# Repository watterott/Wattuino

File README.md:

# Wattuino
Arduino compatible Boards and Modules.

* [Wattuino Board Support Package](https://learn.watterott.com/arduino/watterott-boards) for Arduino IDE.
* [Documentation on learn.watterott.com](https://learn.watterott.com)
* Open-Source and released under the [Creative Commons Attribution Share-Alike License](https://creativecommons.org/licenses/by-sa/4.0/).

## Wattuino RC

* Microchip **SAMW25** Module (SAMD21 ARM Cortex-M0+ and WINC1500 WiFi/WLAN SoC)
* USB CDC+MSC Bootloader (Arduino compatible)
* 5V tolerant IOs
* Dual Full-Bridge Motor Drivers (Allegro Micro A3909)
* MicroUSB connector for programming/communication
* PCB Size: 70mm x 50mm

## Wattuino Uno

* Microchip AVR **ATmega328P** @ 16 MHz (external resonator)
* OptiBoot Bootloader with auto baud rate detection (Arduino compatible)
* FTDI FT231X USB-UART-Bridge
* USB-B or MicroUSB connector for programming/communication
* PCB Size: 68.58mm x 53.34mm

## Wattuino Pro Mini

* Microchip AVR **ATmega328P** @ 16 MHz or 8 MHz (external resonator)
* OptiBoot Bootloader with auto baud rate detection (Arduino compatible)
* All pins of the AVR are available (also ADC6, ADC7)
* FTDI connector for programming/communication
* PCB Size: 33.02mm x 17.78mm

## Wattuino Pro Mini PB

* Microchip AVR **ATmega328PB** @ 16 MHz or 8 MHz (external resonator)
* OptiBoot Bootloader with auto baud rate detection (Arduino compatible)
* All pins of the AVR are available (also PE0/SDA1, PE1/SCL1, PE2/ADC6, PE3/ADC7)
* FTDI connector for programming/communication
* PCB Size: 33.02mm x 17.78mm

## Wattuino Nanite 841

* Microchip AVR **ATtiny841** @ 8 MHz (internal clock) with USART, SPI, I2C Slave, ADC, EEPROM
* Micronucleus USB Bootloader (Arduino compatible)
* Designed by [cpldcpu](https://github.com/cpldcpu)
* 14-Pin DIP and pin-compatible with 14-Pin SOIC ATtiny841
* MicroUSB connector for programming/communication
* PCB Size: 24.13mm x 10.16mm

## Wattuino Nanite 85

* Microchip AVR **ATtiny85** @ 16.5 MHz (internal clock) with USI, ADC, EEPROM
* Micronucleus USB Bootloader (Arduino compatible)
* Based on the original [Nanite 85](https://github.com/cpldcpu/Nanite) design by [cpldcpu](https://github.com/cpldcpu)
* Pin-compatible with 8-Pin DIP ATtiny85
* MicroUSB connector for programming/communication
* PCB Size: 17.46mm x 10.16mm

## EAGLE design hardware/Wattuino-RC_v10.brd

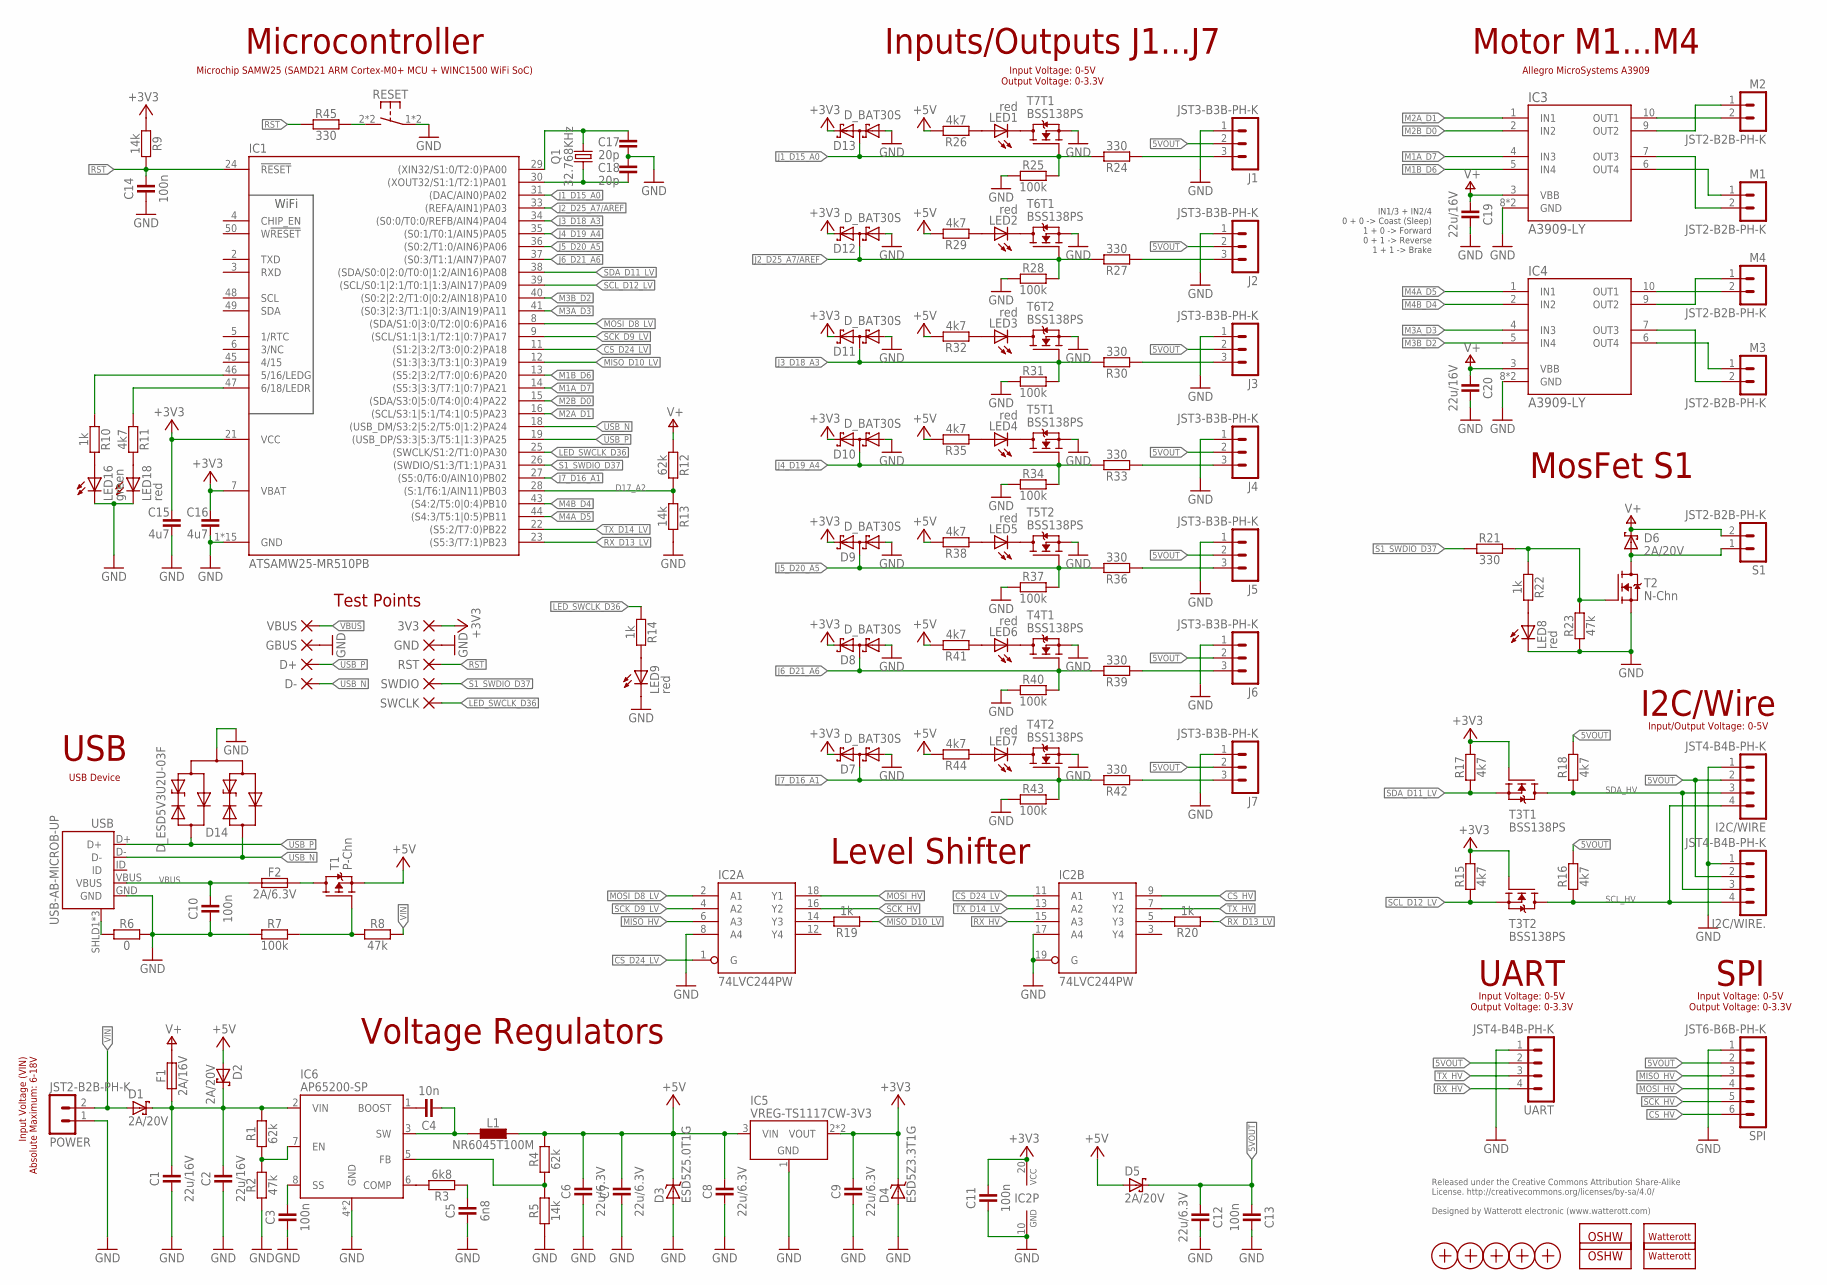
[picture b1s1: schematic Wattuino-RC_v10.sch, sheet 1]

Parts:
3V3: PAD-1.0_NC
C1, C2, C19, C20: 22u/16V; C0805
C3, C10, C11, C13, C14: 100n; C0402
C4: 10n; C0402
C5: 6n8; C0402
C6, C7, C8, C9, C12: 22u/6.3V; C0805
C15, C16: 4u7; C0603
C17, C18: 20p; C0402
D1, D2, D5, D6: 2A/20V; SMA_DO214AC
D3: ESD5Z5.0T1G; SOD523
D4: ESD5Z3.3T1G; SOD523
D7, D8, D9, D10, D11, D12, D13: D_BAT30S; SOT323
D14: D_ESD5V3U2U-03F; SOT723
D+: PAD-1.0_NC
D-: PAD-1.0_NC
F1: 2A/16V; C1812
F2: 2A/6.3V; C1206
GBUS: PAD-1.0_NC
GND: PAD-1.0_NC
I2C/WIRE, I2C/WIRE.: JST4-B4B-PH-K; JST_B4B-PH-K
IC1: ATSAMW25-MR510PB; ATSAMW25-MRX10
IC2: 74LVC244PW; TSSOP20
IC3, IC4: A3909-LY; MSOP10-PAD
IC5: VREG-TS1117CW-3V3; SOT223
IC6: AP65200-SP; SO08-PAD
J1, J2, J3, J4, J5, J6, J7: JST3-B3B-PH-K; JST_B3B-PH-K
L1: NR6045T100M; L_NR60XX
LED1, LED2, LED3, LED4, LED5, LED6, LED7, LED8, LED9, LED18: red; C0603
LED16: green; C0603
LOGO1: OSHW_LOGOX0100; OSHW_6X100
LOGO2: OSHW_LOGOX0150; OSHW_6X150
LOGO3: LOGO-S_PLACE_S; SPARK_TPLACE_S
LOGO4: LOGO-PLACE; LOGO_TPLACE
M1, M2, M3, M4: JST2-B2B-PH-K; JST_B2B-PH-K
POWER: JST2-B2B-PH-K; JST_B2B-PH-K
Q1: 32.768KHz; CRYSTAL_ZM315
R1, R4, R12: 62k; C0402
R2, R8, R23: 47k; C0402
R3: 6k8; C0402
R5, R9, R13: 14k; C0402
R6: 0; C0402
R7, R25, R28, R31, R34, R37, R40, R43: 100k; C0402
R10, R14, R19, R20, R22: 1k; C0402
R11, R15, R16, R17, R18, R26, R29, R32, R35, R38, R41, R44: 4k7; C0402
R21, R24, R27, R30, R33, R36, R39, R42, R45: 330; C0402
RESET: SW-TACTILE-TL3305C; TL3305; MPN TL3305C
RST: PAD-1.0_NC
S1: JST2-B2B-PH-K; JST_B2B-PH-K
SPI: JST6-B6B-PH-K; JST_B6B-PH-K
SWCLK: PAD-1.0_NC
SWDIO: PAD-1.0_NC
T1: P-Chn; SOT23
T2: N-Chn; SOT23
T3, T4, T5, T6, T7: BSS138PS; SOT363
UART: JST4-B4B-PH-K; JST_B4B-PH-K
USB: USB-AB-MICROB-UP; USB-MICROB-1051330011
VBUS: PAD-1.0_NC
X1, X2, X3, X4: PASSER-07; PASSER_07MM
X5: PASSER-04; PASSER_04MM

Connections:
5VOUT: C12.2, C13.2, D5.C, I2C/WIRE.2, I2C/WIRE..2, J1.2, J2.2, J3.2, J4.2, J5.2, J6.2, J7.2, R16.2, R18.2, SPI.2, UART.2
+3V3: 3V3.1, C9.2, C11.2, C15.2, C16.2, D4.C, D7.2 (C), D8.2 (C), D9.2 (C), D10.2 (C), D11.2 (C), D12.2 (C), D13.2 (C), IC1.7 (VBAT), IC1.21 (VCC), IC2.20 (VCC), IC5.2 (VOUT), IC5.4 (VOUT), R9.1, R15.2, R17.2, T3.2 (G), T3.5 (G)
+5V: C6.2, C7.2, C8.2, D2.A, D3.C, D5.A, IC5.3 (VIN), L1.2, R4.2, R26.2, R29.2, R32.2, R35.2, R38.2, R41.2, R44.2, T1.2 (S)
BOOST: C4.2, IC6.1 (BOOST)
COMP: IC6.6 (COMP), R3.2
CS_D24_LV: IC1.11 ((S1:2|3:2/T3:0|0:2)PA18), IC2.1 (G), IC2.11 (A1)
CS_HV: IC2.9 (Y1), SPI.6
D17_A2: IC1.28 ((S:1/T6:1/AIN11)PB03), R12.2, R13.1
GND: C1.1, C2.1, C3.1, C5.1, C6.1, C7.1, C8.1, C9.1, C10.1, C11.1, C12.1, C13.1, C14.1, C15.1, C16.1, C17.2, C18.2, C19.2, C20.2, D3.A, D4.A, D7.1 (A), D8.1 (A), D9.1 (A), D10.1 (A), D11.1 (A), D12.1 (A), D13.1 (A), D14.3 (A), GBUS.1, GND.1, I2C/WIRE.1, I2C/WIRE..1, IC1.1 (GND), IC1.10 (GND), IC1.17 (GND), IC1.20 (GND), IC1.32 (GND), IC1.42 (GND), IC1.51 (GND), IC1.GND@1 (GND), IC1.GND@2 (GND), IC1.GND@3 (GND), IC1.GND@4 (GND), IC1.GND@5 (GND), IC1.GND@6 (GND), IC1.GND@7 (GND), IC1.GND@8 (GND), IC2.8 (A4), IC2.10 (GND), IC2.17 (A4), IC2.19 (G), IC3.8 (GND), IC3.TP (GND), IC4.8 (GND), IC4.TP (GND), IC5.1 (GND), IC6.4 (GND), IC6.TP (GND), J1.1, J2.1, J3.1, J4.1, J5.1, J6.1, J7.1, LED8.C, LED9.C, LED16.C, LED18.C, POWER.1 (2), R2.1, R5.1, R6.1, R7.1, R13.2, R23.1, R25.1, R28.1, R31.1, R34.1, R37.1, R40.1, R43.1, RESET.1, RESET.4 (P1), SPI.1, T2.2 (S), T4.1 (S), T4.4 (S), T5.1 (S), T5.4 (S), T6.1 (S), T6.4 (S), T7.1 (S), UART.1, USB.GND
IO16: IC1.46 (5/16/LEDG), R10.1
IO18: IC1.47 (6/18/LEDR), R11.1
J1_D15_A0: D13.3 (CA), IC1.31 ((DAC/AIN0)PA02), R24.2, R25.2, T7.2 (G)
J2_D25_A7/AREF: D12.3 (CA), IC1.33 ((REFA/AIN1)PA03), R27.2, R28.2, T6.2 (G)
J3_D18_A3: D11.3 (CA), IC1.34 ((S0:0/T0:0/REFB/AIN4)PA04), R30.2, R31.2, T6.5 (G)
J4_D19_A4: D10.3 (CA), IC1.35 ((S0:1/T0:1/AIN5)PA05), R33.2, R34.2, T5.2 (G)
J5_D20_A5: D9.3 (CA), IC1.36 ((S0:2/T1:0/AIN6)PA06), R36.2, R37.2, T5.5 (G)
J6_D21_A6: D8.3 (CA), IC1.37 ((S0:3/T1:1/AIN7)PA07), R39.2, R40.2, T4.2 (G)
J7_D16_A1: D7.3 (CA), IC1.27 ((S5:0/T6:0/AIN10)PB02), R42.2, R43.2, T4.5 (G)
LED_SWCLK_D36: IC1.25 ((SWCLK/S1:2/T1:0)PA30), R14.1, SWCLK.1
M1A_D7: IC1.14 ((S5:3|3:3/T7:1|0:7)PA21), IC3.4 (IN3)
M1B_D6: IC1.13 ((S5:2|3:2/T7:0|0:6)PA20), IC3.5 (IN4)
M1_O1: IC3.7 (OUT3), M1.2 (1)
M1_O2: IC3.6 (OUT4), M1.1 (2)
M2A_D1: IC1.16 ((SCL/S3:1|5:1/T4:1|0:5)PA23), IC3.1 (IN1)
M2B_D0: IC1.15 ((SDA/S3:0|5:0/T4:0|0:4)PA22), IC3.2 (IN2)
M2_O1: IC3.10 (OUT1), M2.2 (1)
M2_O2: IC3.9 (OUT2), M2.1 (2)
M3A_D3: IC1.41 ((S0:3|2:3/T1:1|0:3/AIN19)PA11), IC4.4 (IN3)
M3B_D2: IC1.40 ((S0:2|2:2/T1:0|0:2/AIN18)PA10), IC4.5 (IN4)
M3_O1: IC4.7 (OUT3), M3.2 (1)
M3_O2: IC4.6 (OUT4), M3.1 (2)
M4A_D5: IC1.44 ((S4:3/T5:1|0:5)PB11), IC4.1 (IN1)
M4B_D4: IC1.43 ((S4:2/T5:0|0:4)PB10), IC4.2 (IN2)
M4_O1: IC4.10 (OUT1), M4.2 (1)
M4_O2: IC4.9 (OUT2), M4.1 (2)
MISO_D10_LV: IC1.12 ((S1:3|3:3/T3:1|0:3)PA19), R19.1
MISO_HV: IC2.6 (A3), SPI.3
MISO_LV: IC2.14 (Y3), R19.2
MOSI_D8_LV: IC1.8 ((SDA/S1:0|3:0/T2:0|0:6)PA16), IC2.2 (A1)
MOSI_HV: IC2.18 (Y1), SPI.4
unnamed: LED8.A, R22.2
unnamed: J1.3, R24.1
unnamed: F2.2, T1.3 (D)
unnamed: R7.2, R8.1, T1.1 (G)
unnamed: LED9.A, R14.2
unnamed: R21.2, R22.1, R23.2, T2.1 (G)
unnamed: LED7.C, T4.3 (D)
unnamed: LED7.A, R44.1
unnamed: J7.3, R42.1
unnamed: C4.1, IC6.3 (SW), L1.1
unnamed: C3.2, IC6.8 (SS)
unnamed: J6.3, R39.1
unnamed: J5.3, R36.1
unnamed: J4.3, R33.1
unnamed: IC6.5 (FB), R4.1, R5.2
unnamed: LED6.C, T4.6 (D)
unnamed: LED6.A, R41.1
unnamed: J2.3, R27.1
unnamed: LED5.A, R38.1
unnamed: J3.3, R30.1
unnamed: LED4.A, R35.1
unnamed: LED4.C, T5.6 (D)
unnamed: LED5.C, T5.3 (D)
unnamed: LED3.A, R32.1
unnamed: LED2.A, R29.1
unnamed: LED2.C, T6.6 (D)
unnamed: LED3.C, T6.3 (D)
unnamed: LED1.A, R26.1
unnamed: LED1.C, T7.6 (D)
unnamed: C5.2, R3.1
unnamed: IC6.7 (EN), R1.1, R2.2
unnamed: LED18.A, R11.2
unnamed: LED16.A, R10.2
RST: C14.2, IC1.24 (!RESET), R9.2, R45.1, RST.1
RST_SW: R45.2, RESET.2 (S1), RESET.3 (S1)
RX_D13_LV: IC1.23 ((S5:3/T7:1)PB23), R20.1
RX_HV: IC2.15 (A3), UART.4
RX_LV: IC2.5 (Y3), R20.2
S1: D6.A, S1.1 (2), T2.3 (D)
S1_SWDIO_D37: IC1.26 ((SWDIO/S1:3/T1:1)PA31), R21.1, SWDIO.1
SCK_D9_LV: IC1.9 ((SCL/S1:1|3:1/T2:1|0:7)PA17), IC2.4 (A2)
SCK_HV: IC2.16 (Y2), SPI.5
SCL_D12_LV: IC1.39 ((SCL/S0:1|2:1/T0:1|1:3/AIN17)PA09), R15.1, T3.4 (S)
SCL_HV: I2C/WIRE.4, I2C/WIRE..4, R16.1, T3.3 (D)
SDA_D11_LV: IC1.38 ((SDA/S0:0|2:0/T0:0|1:2/AIN16)PA08), R17.1, T3.1 (S)
SDA_HV: I2C/WIRE.3, I2C/WIRE..3, R18.1, T3.6 (D)
SHLD1: R6.2, USB.SHLD1 (SHIELD), USB.SHLD2 (SHIELD), USB.SHLD3 (SHIELD)
TX_D14_LV: IC1.22 ((S5:2/T7:0)PB22), IC2.13 (A2)
TX_HV: IC2.7 (Y2), UART.3
USB_N: D14.1 (C1), D-.1, IC1.18 ((USB_DM/S3:2|5:2/T5:0|1:2)PA24), USB.D-
USB_P: D14.2 (C2), D+.1, IC1.19 ((USB_DP/S3:3|5:3/T5:1|1:3)PA25), USB.D+
V+: C19.1, C20.1, D6.C, F1.2, IC3.3 (VBB), IC4.3 (VBB), R12.1, S1.2 (1)
VBUS: C10.2, F2.1, USB.VBUS, VBUS.1
VIN: D1.A, POWER.2 (1), R8.2
VINP: C1.2, C2.2, D1.C, D2.C, F1.1, IC6.2 (VIN), R1.2
XIN: C17.1, IC1.29 ((XIN32/S1:0/T2:0)PA00), Q1.2
XOUT: C18.1, IC1.30 ((XOUT32/S1:1/T2:1)PA01), Q1.1

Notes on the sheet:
USB
Motor M1...M4
MosFet S1
I2C/Wire
UART
SPI
Inputs/Outputs J1...J7
Voltage Regulators
Microcontroller
Test Points
Released under the Creative Commons Attribution Share-Alike License. http://creativecommons.org/licenses/by-sa/4.0/ Designed by Watterott electronic (www.watterott.com)
Input Voltage (VIN) Absolute Maximum: 6-18V
Level Shifter
Input Voltage: 0-5V Output Voltage: 0-3.3V
Allegro MicroSystems A3909
Input/Output Voltage: 0-5V
Microchip SAMW25 (SAMD21 ARM Cortex-M0+ MCU + WINC1500 WiFi SoC)
IN1/3 + IN2/4 0 + 0 -> Coast (Sleep) 1 + 0 -> Forward 0 + 1 -> Reverse 1 + 1 -> Brake
USB Device

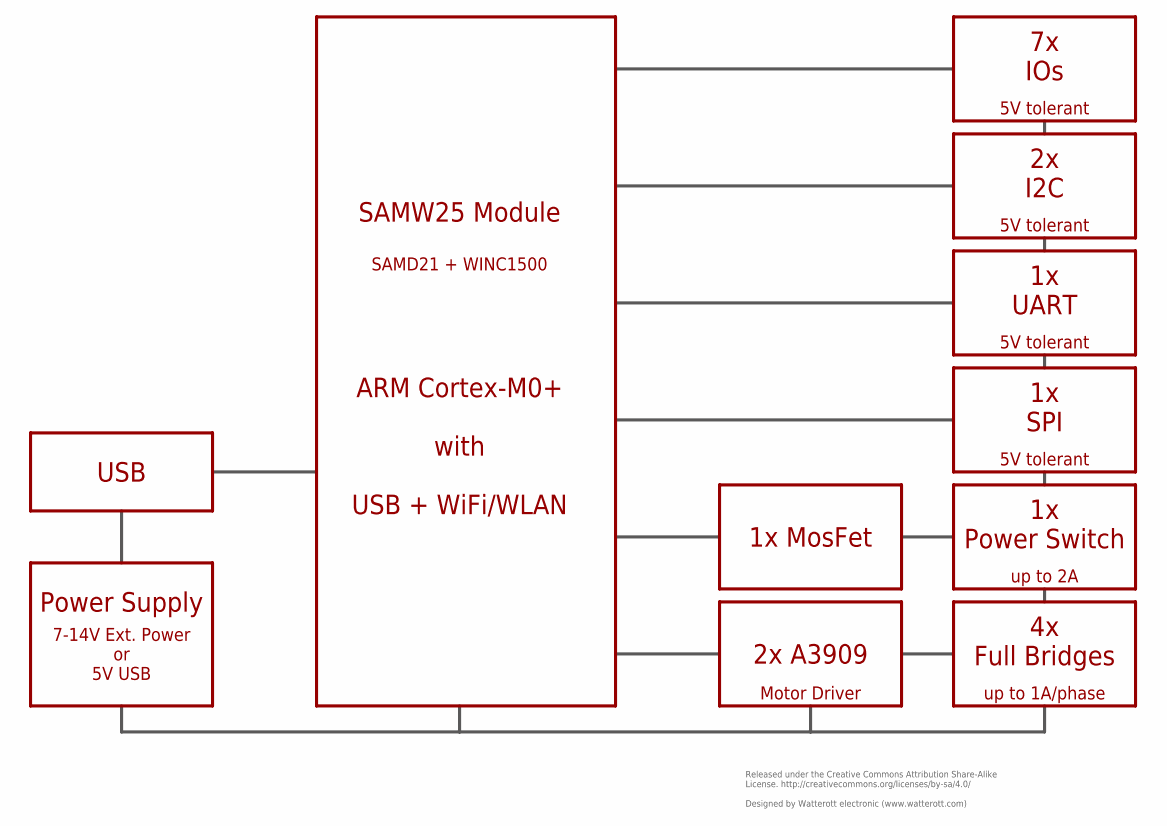
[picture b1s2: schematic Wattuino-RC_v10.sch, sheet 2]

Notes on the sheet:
SAMD21 + WINC1500
SAMW25 Module
USB
ARM Cortex-M0+ with USB + WiFi/WLAN
2x A3909
Motor Driver
7x IOs
2x I2C
1x UART
1x SPI
4x Full Bridges
1x Power Switch
1x MosFet
Power Supply
7-14V Ext. Power or 5V USB
5V tolerant
up to 2A
up to 1A/phase
Released under the Creative Commons Attribution Share-Alike License. http://creativecommons.org/licenses/by-sa/4.0/ Designed by Watterott electronic (www.watterott.com)

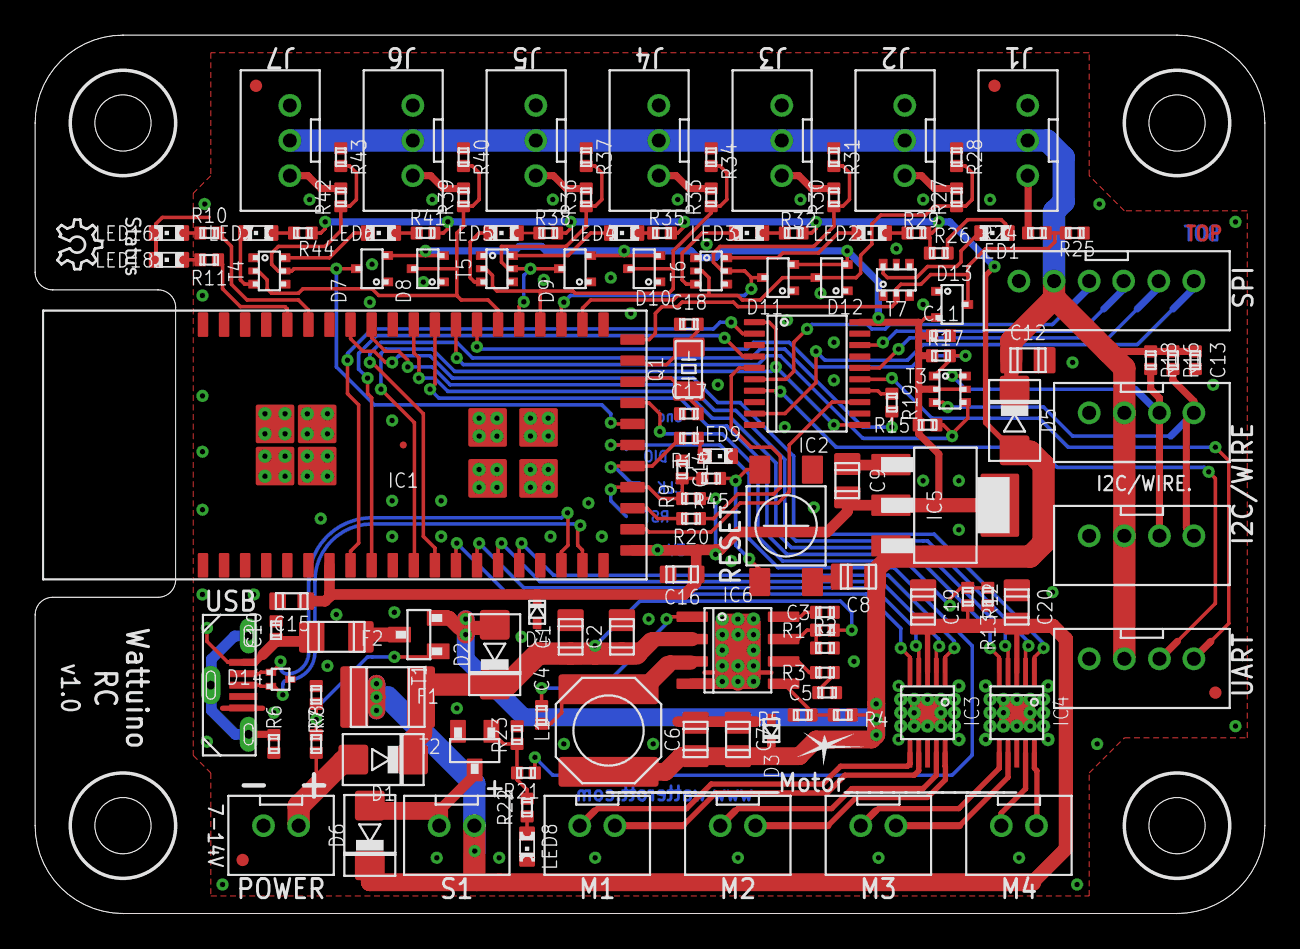
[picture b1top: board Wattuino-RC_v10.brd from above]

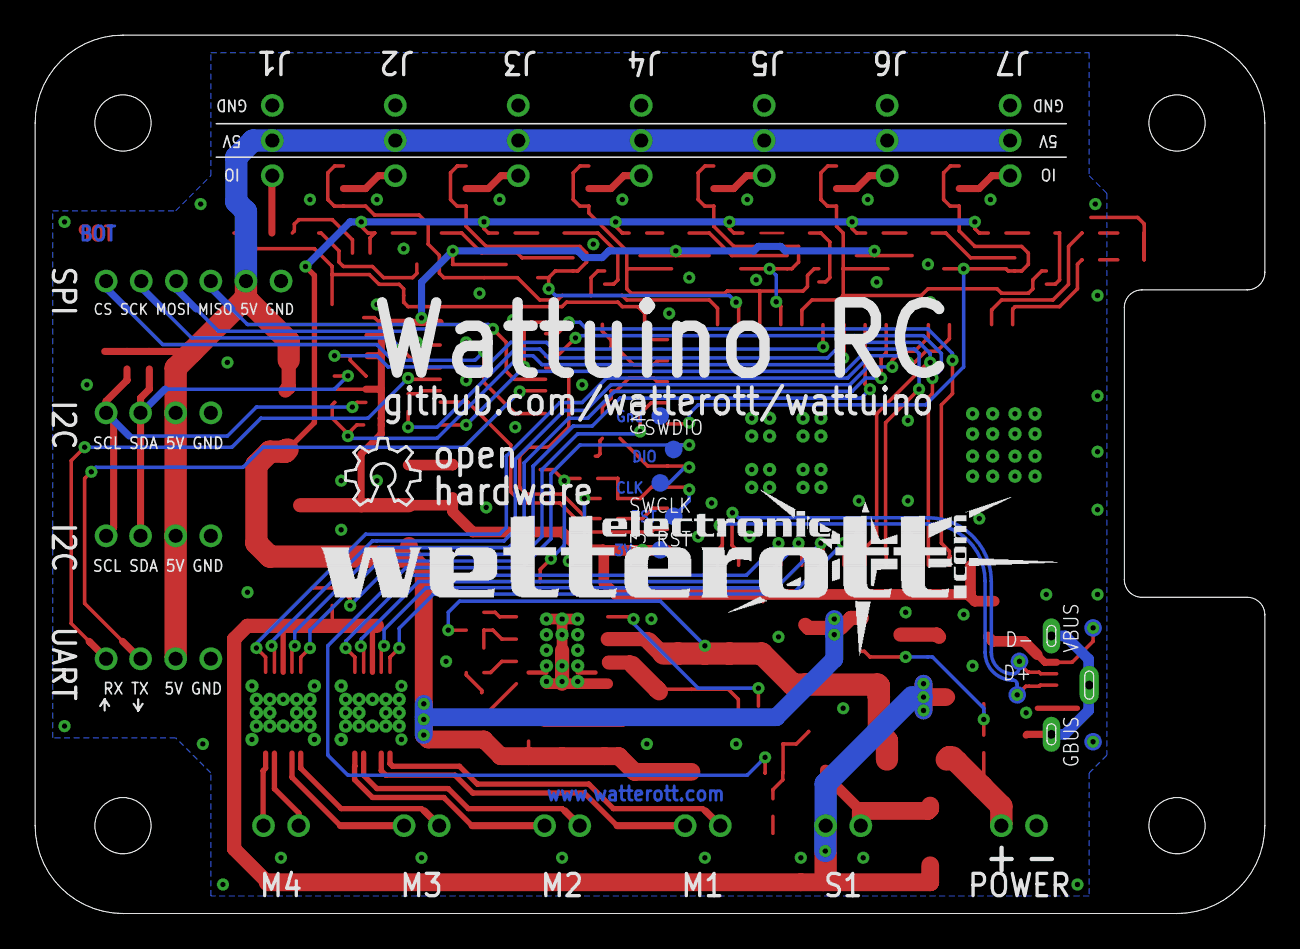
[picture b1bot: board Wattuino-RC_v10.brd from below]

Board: 2 copper layers, 70.0 x 50.0 mm, 144 parts (11 on the bottom side), 97 nets.

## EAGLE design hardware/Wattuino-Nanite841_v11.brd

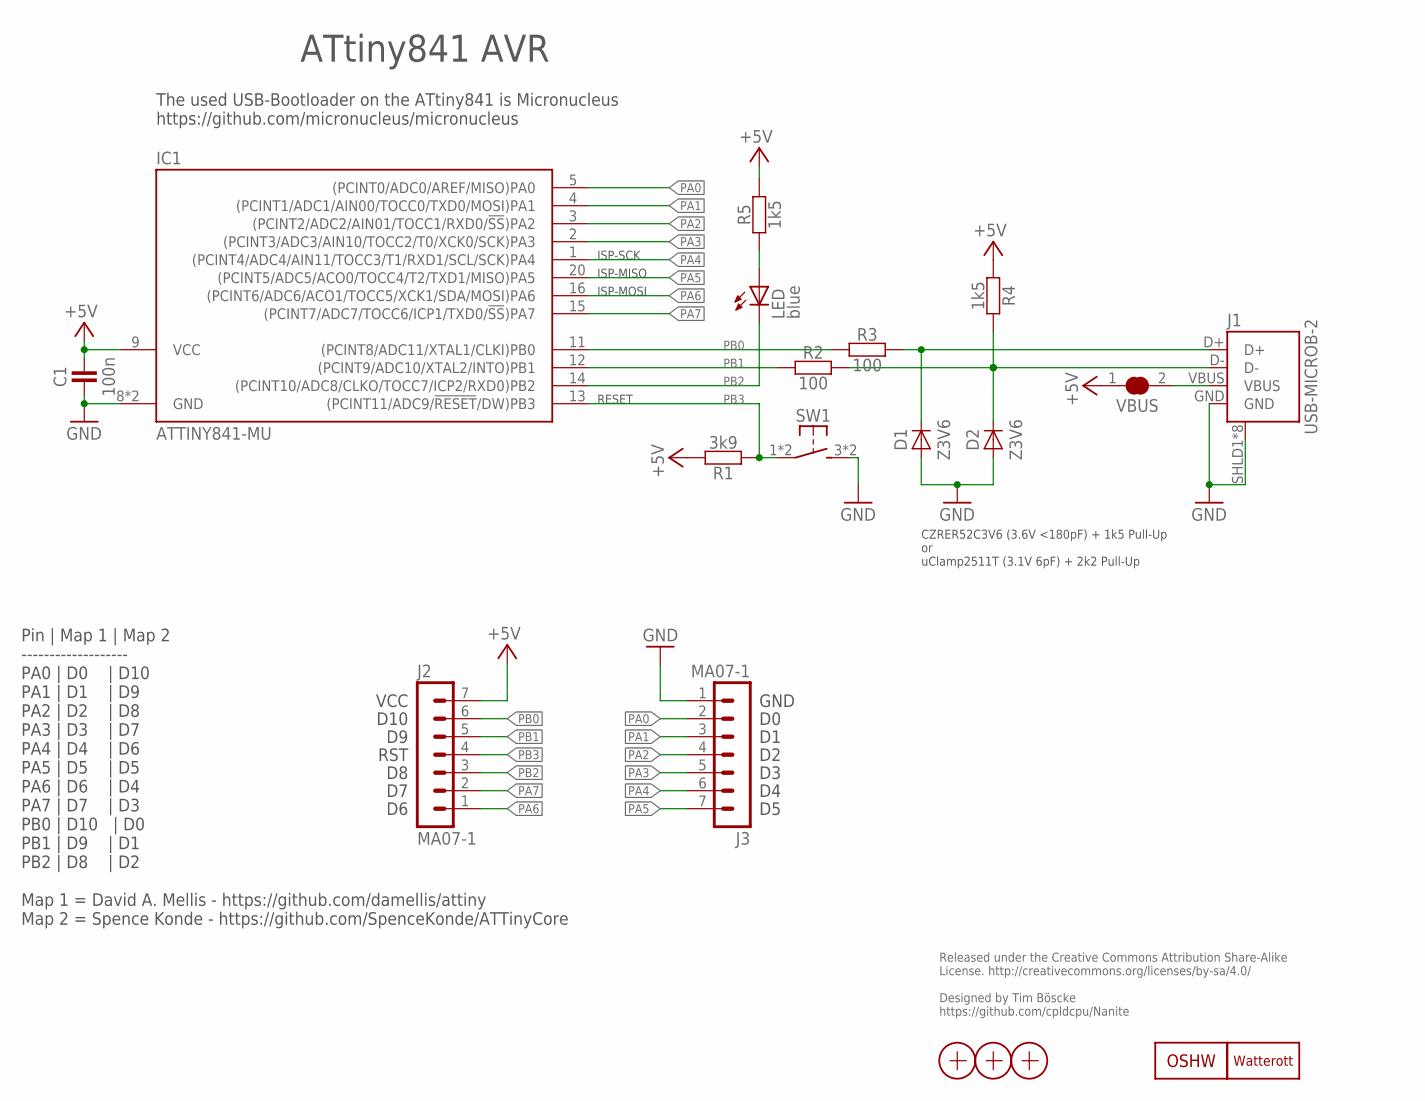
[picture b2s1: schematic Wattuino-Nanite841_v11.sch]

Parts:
C1: 100n; C0402
D1, D2: Z3V6; SOD882
IC1: ATTINY841-MU; QFN20-PAD
J1: USB-MICROB-2; USB-MICROB-10118194
J2, J3: MA07-1
LED: blue; C0603
LOGO1: LOGO-S_PLACE_S; SPARK_TPLACE_S
LOGO2: OSHW_LOGOX0070; OSHW_6X70
R1: 3k9; C0402
R2, R3: 100; C0402
R4, R5: 1k5; C0402
SW1: SW-TACTILE-PTS840P; PTS840P
VBUS: JUMPER2-0603-NC; JUMPER2-0603_NC
X1, X2, X3: PASSER-07; PASSER_07MM

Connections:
+5V: C1.2, IC1.9 (VCC), J2.7, R1.2, R4.1, R5.2, VBUS.1
D_N: D2.C, J1.D-, R2.2, R4.2
D_P: D1.C, J1.D+, R3.2
GND: C1.1, D1.A, D2.A, IC1.8 (GND), IC1.TP (GND), J1.GND, J1.SHLD1 (SHIELD), J1.SHLD2 (SHIELD), J1.SHLD3 (SHIELD), J1.SHLD4 (SHIELD), J1.SHLD5 (SHIELD), J1.SHLD6 (SHIELD), J1.SHLD7 (SHIELD), J1.SHLD8 (SHIELD), J3.1, SW1.3 (S1), SW1.4 (S1)
LED+: LED.A, R5.1
PA0: IC1.5 ((PCINT0/ADC0/AREF/MISO)PA0), J3.2
PA1: IC1.4 ((PCINT1/ADC1/AIN00/TOCC0/TXD0/MOSI)PA1), J3.3
PA2: IC1.3 ((PCINT2/ADC2/AIN01/TOCC1/RXD0/!SS!)PA2), J3.4
PA3: IC1.2 ((PCINT3/ADC3/AIN10/TOCC2/T0/XCK0/SCK)PA3), J3.5
PA4: IC1.1 ((PCINT4/ADC4/AIN11/TOCC3/T1/RXD1/SCL/SC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), J3.6
PA5: IC1.20 ((PCINT5/ADC5/ACO0/TOCC4/T2/TXD1/MISO)PA5), J3.7
PA6: IC1.16 ((PCINT6/ADC6/ACO1/TOCC5/XCK1/SDA/MOSI)P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), J2.1
PA7: IC1.15 ((PCINT7/ADC7/TOCC6/ICP1/TXD0/!SS!)PA7), J2.2
PB0: IC1.11 ((PCINT8/ADC11/XTAL1/CLKI)PB0), J2.6, R3.1
PB1: IC1.12 ((PCINT9/ADC10/XTAL2/INTO)PB1), J2.5, R2.1
PB2: IC1.14 ((PCINT10/ADC8/CLKO/TOCC7/ICP2/RXD0)PB2), J2.3, LED.C
PB3: IC1.13 ((PCINT11/ADC9/!RESET!/DW)PB3), J2.4, R1.1, SW1.1, SW1.2 (P1)
VBUS: J1.VBUS, VBUS.2

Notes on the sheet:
Released under the Creative Commons Attribution Share-Alike License. http://creativecommons.org/licenses/by-sa/4.0/ Designed by Tim Böscke https://github.com/cpldcpu/Nanite
The used USB-Bootloader on the ATtiny841 is Micronucleus https://github.com/micronucleus/micronucleus
CZRER52C3V6 (3.6V <180pF) + 1k5 Pull-Up or uClamp2511T (3.1V 6pF) + 2k2 Pull-Up
ATtiny841 AVR
GND
VCC
D10
RST
RESET
Pin | Map 1 | Map 2 ------------------- PA0 | D0 | D10 PA1 | D1 | D9 PA2 | D2 | D8 PA3 | D3 | D7 PA4 | D4 | D6 PA5 | D5 | D5 PA6 | D6 | D4 PA7 | D7 | D3 PB0 | D10 | D0 PB1 | D9 | D1 PB2 | D8 | D2 Map 1 = David A. Mellis - https://github.com/damellis/attiny Map 2 = Spence Konde - https://github.com/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
ISP-MOSI
ISP-MISO
ISP-SCK

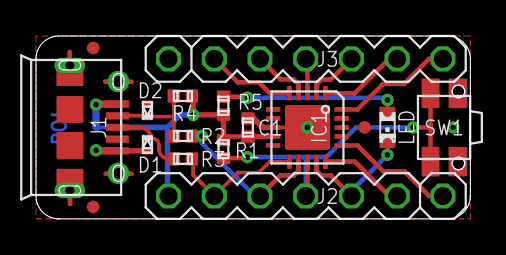
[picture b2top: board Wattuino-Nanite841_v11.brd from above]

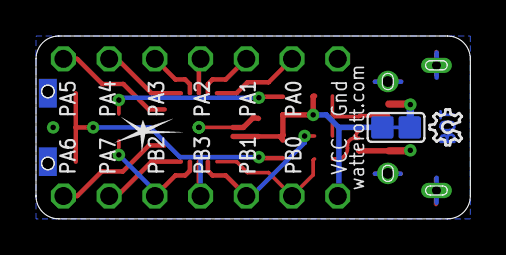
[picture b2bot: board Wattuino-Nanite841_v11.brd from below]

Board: 2 copper layers, 24.1 x 10.2 mm, 20 parts (3 on the bottom side), 18 nets.

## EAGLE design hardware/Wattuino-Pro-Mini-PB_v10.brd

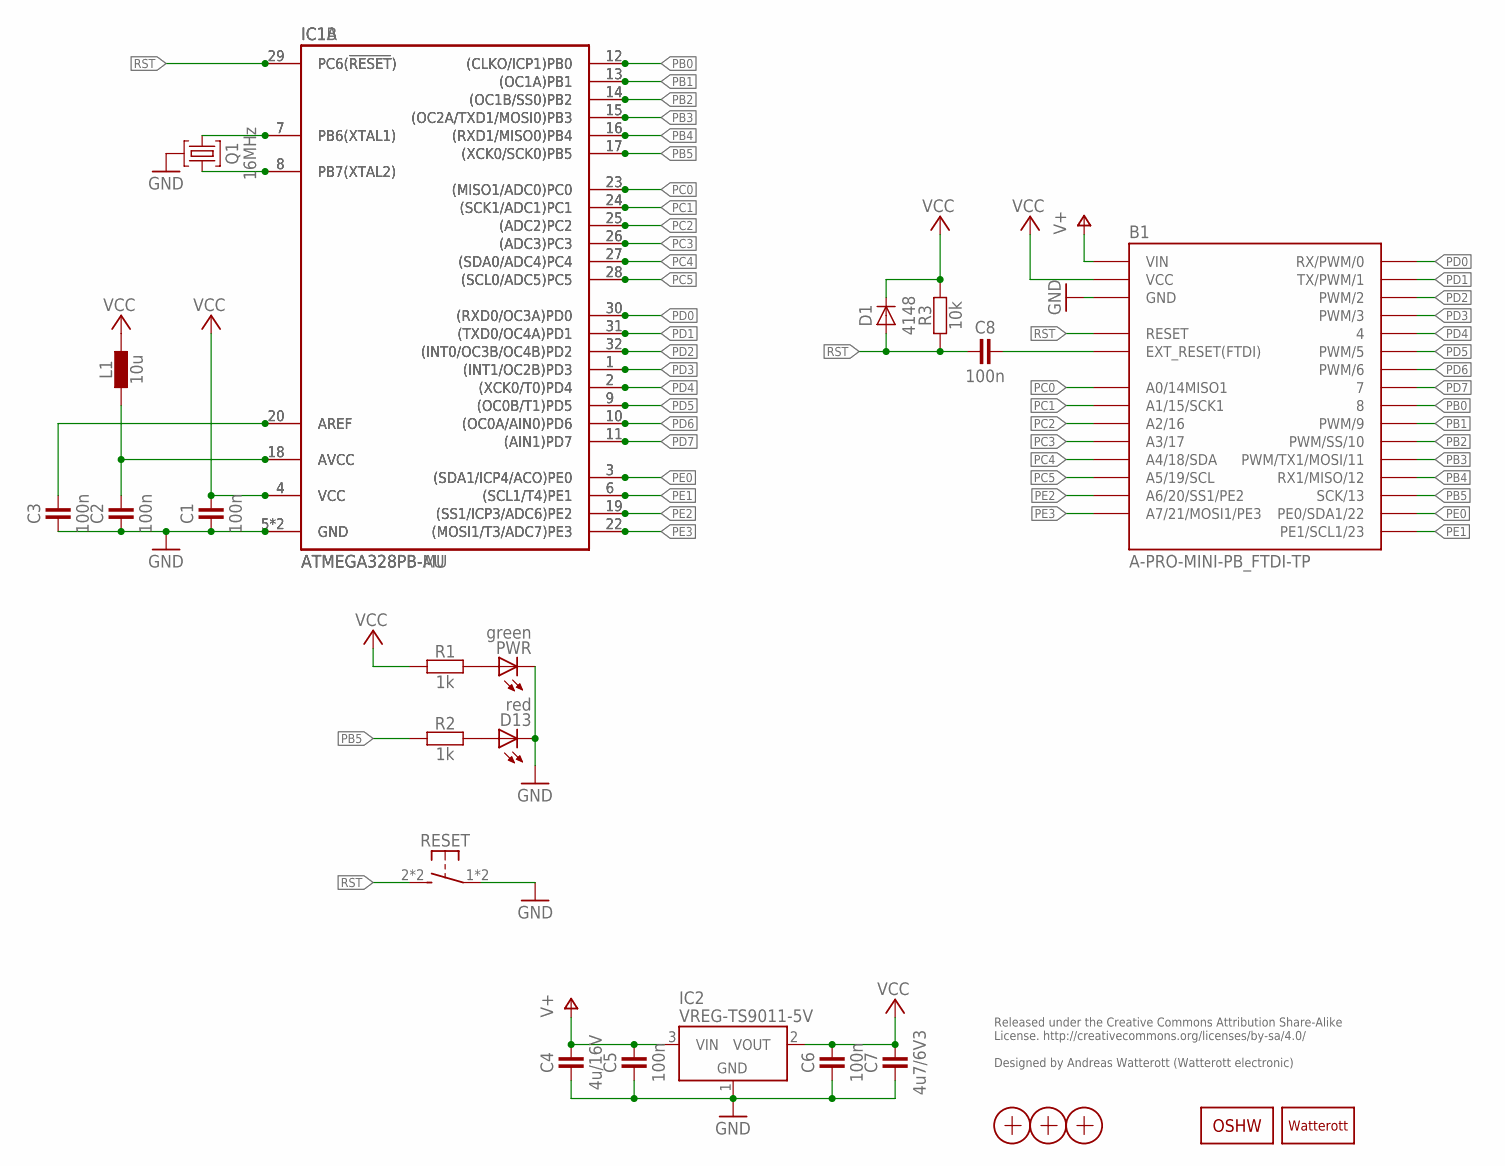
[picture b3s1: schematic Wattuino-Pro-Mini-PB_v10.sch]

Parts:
B1: A-PRO-MINI-PB_FTDI-TP; A-PRO-MINI-PB-FTDI_TP
C1, C2, C3, C5, C6, C8: 100n; C0402
C4: 4u/16V; C0805
C7: 4u7/6V3; C0402
D1: 4148; SOD882
D13: red; C0603
IC1A: ATMEGA328PB-AU; TQFP32
IC1B: ATMEGA328PB-MU; QFN32-PAD
IC2: VREG-TS9011-5V; SOT23
L1: 10u; C0603
LOGO1: OSHW_LOGOX0070; OSHW_6X70
LOGO2: LOGO-S_PLACE_S; SPARK_TPLACE_S
PWR: green; C0603
Q1: 16MHz; CRYSTAL_32X13
R1, R2: 1k; C0402
R3: 10k; C0402
RESET: SW-TACTILE-TL3315; TL3315N
X1, X2, X3: PASSER-07; PASSER_07MM

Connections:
AREF: C3.2, IC1A.20 (AREF), IC1B.20 (AREF)
AVCC: C2.2, IC1A.18 (AVCC), IC1B.18 (AVCC), L1.1
GND: B1.GND@1 (GND), B1.GND@2 (GND), B1.GND@3 (GND), B1.GND@4 (GND), C1.1, C2.1, C3.1, C4.1, C5.1, C6.1, C7.1, D13.C, IC1A.5 (GND), IC1A.21 (GND), IC1B.5 (GND), IC1B.21 (GND), IC2.1 (GND), PWR.C, Q1.GND, RESET.1, RESET.4 (P1)
unnamed: IC1A.8 (PB7(XTAL2)), IC1B.8 (PB7(XTAL2)), Q1.1
unnamed: IC1A.7 (PB6(XTAL1)), IC1B.7 (PB6(XTAL1)), Q1.2
unnamed: PWR.A, R1.2
unnamed: D13.A, R2.2
unnamed: B1.EXT_RST (EXT_RESET(FTDI)), C8.2
PB0: B1.8, IC1A.12 ((CLKO/ICP1)PB0), IC1B.12 ((CLKO/ICP1)PB0)
PB1: B1.9 (PWM/9), IC1A.13 ((OC1A)PB1), IC1B.13 ((OC1A)PB1)
PB2: B1.10 (PWM/SS/10), IC1A.14 ((OC1B/SS0)PB2), IC1B.14 ((OC1B/SS0)PB2)
PB3: B1.11 (PWM/TX1/MOSI/11), IC1A.15 ((OC2A/TXD1/MOSI0)PB3), IC1B.15 ((OC2A/TXD1/MOSI0)PB3)
PB4: B1.12 (RX1/MISO/12), IC1A.16 ((RXD1/MISO0)PB4), IC1B.16 ((RXD1/MISO0)PB4)
PB5: B1.13 (SCK/13), IC1A.17 ((XCK0/SCK0)PB5), IC1B.17 ((XCK0/SCK0)PB5), R2.1
PC0: B1.A0 (A0/14MISO1), IC1A.23 ((MISO1/ADC0)PC0), IC1B.23 ((MISO1/ADC0)PC0)
PC1: B1.A1 (A1/15/SCK1), IC1A.24 ((SCK1/ADC1)PC1), IC1B.24 ((SCK1/ADC1)PC1)
PC2: B1.A2 (A2/16), IC1A.25 ((ADC2)PC2), IC1B.25 ((ADC2)PC2)
PC3: B1.A3 (A3/17), IC1A.26 ((ADC3)PC3), IC1B.26 ((ADC3)PC3)
PC4: B1.A4 (A4/18/SDA), IC1A.27 ((SDA0/ADC4)PC4), IC1B.27 ((SDA0/ADC4)PC4)
PC5: B1.A5 (A5/19/SCL), IC1A.28 ((SCL0/ADC5)PC5), IC1B.28 ((SCL0/ADC5)PC5)
PD0: B1.RXD@1 (RX/PWM/0), B1.RXD@2 (RX/PWM/0), IC1A.30 ((RXD0/OC3A)PD0), IC1B.30 ((RXD0/OC3A)PD0)
PD1: B1.TXD@1 (TX/PWM/1), B1.TXD@2 (TX/PWM/1), IC1A.31 ((TXD0/OC4A)PD1), IC1B.31 ((TXD0/OC4A)PD1)
PD2: B1.2 (PWM/2), IC1A.32 ((INT0/OC3B/OC4B)PD2), IC1B.32 ((INT0/OC3B/OC4B)PD2)
PD3: B1.3 (PWM/3), IC1A.1 ((INT1/OC2B)PD3), IC1B.1 ((INT1/OC2B)PD3)
PD4: B1.4, IC1A.2 ((XCK0/T0)PD4), IC1B.2 ((XCK0/T0)PD4)
PD5: B1.5 (PWM/5), IC1A.9 ((OC0B/T1)PD5), IC1B.9 ((OC0B/T1)PD5)
PD6: B1.6 (PWM/6), IC1A.10 ((OC0A/AIN0)PD6), IC1B.10 ((OC0A/AIN0)PD6)
PD7: B1.7, IC1A.11 ((AIN1)PD7), IC1B.11 ((AIN1)PD7)
PE0: B1.PE0 (PE0/SDA1/22), IC1A.3 ((SDA1/ICP4/ACO)PE0), IC1B.3 ((SDA1/ICP4/ACO)PE0)
PE1: B1.PE1 (PE1/SCL1/23), IC1A.6 ((SCL1/T4)PE1), IC1B.6 ((SCL1/T4)PE1)
PE2: B1.A6 (A6/20/SS1/PE2), IC1A.19 ((SS1/ICP3/ADC6)PE2), IC1B.19 ((SS1/ICP3/ADC6)PE2)
PE3: B1.A7 (A7/21/MOSI1/PE3), IC1A.22 ((MOSI1/T3/ADC7)PE3), IC1B.22 ((MOSI1/T3/ADC7)PE3)
RST: B1.RST@1 (RESET), B1.RST@2 (RESET), C8.1, D1.A, IC1A.29 (PC6(!RESET!)), IC1B.29 (PC6(!RESET!)), R3.1, RESET.2 (S1), RESET.3 (S1)
V+: B1.VIN, C4.2, C5.2, IC2.3 (VIN)
VCC: B1.VCC@1 (VCC), B1.VCC@2 (VCC), C1.2, C6.2, C7.2, D1.C, IC1A.4 (VCC), IC1B.4 (VCC), IC2.2 (VOUT), L1.2, R1.1, R3.2

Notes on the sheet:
Released under the Creative Commons Attribution Share-Alike License. http://creativecommons.org/licenses/by-sa/4.0/ Designed by Andreas Watterott (Watterott electronic)

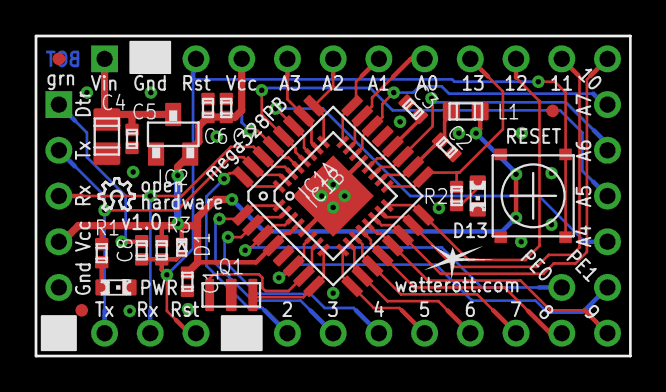
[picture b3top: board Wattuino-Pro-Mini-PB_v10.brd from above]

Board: 2 copper layers, 33.0 x 17.8 mm, 26 parts (0 on the bottom side), 35 nets.

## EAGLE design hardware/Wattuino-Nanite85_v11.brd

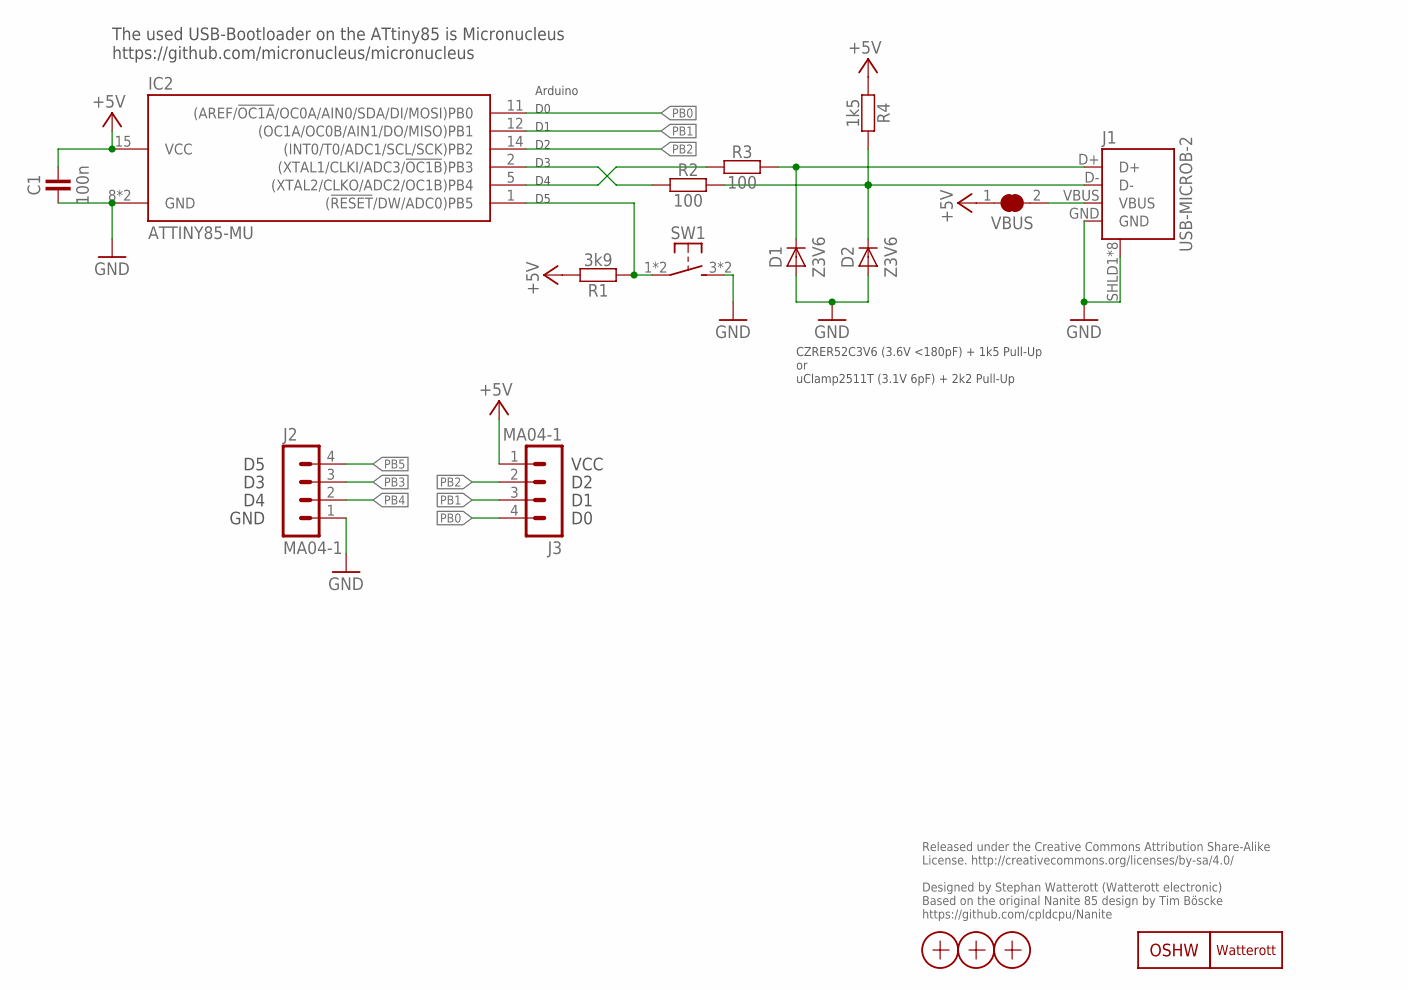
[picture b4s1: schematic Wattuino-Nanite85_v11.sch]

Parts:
C1: 100n; C0402
D1, D2: Z3V6; SOD882
IC2: ATTINY85-MU; QFN20-PAD
J1: USB-MICROB-2; USB-MICROB-10118194
J2, J3: MA04-1
LOGO1: LOGO-S_PLACE_S; SPARK_TPLACE_S
LOGO2: OSHW_LOGOX0070; OSHW_6X70
R1: 3k9; C0402
R2, R3: 100; C0402
R4: 1k5; C0402
SW1: SW-TACTILE-PTS840P; PTS840P
VBUS: JUMPER2-0603-NC; JUMPER2-0603_NC
X1, X2, X3: PASSER-07; PASSER_07MM

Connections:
+5V: C1.2, IC2.15 (VCC), J3.1, R1.2, R4.1, VBUS.1
D_N: D2.C, J1.D-, R2.2, R4.2
D_P: D1.C, J1.D+, R3.2
GND: C1.1, D1.A, D2.A, IC2.8 (GND), IC2.TP (GND), J1.GND, J1.SHLD1 (SHIELD), J1.SHLD2 (SHIELD), J1.SHLD3 (SHIELD), J1.SHLD4 (SHIELD), J1.SHLD5 (SHIELD), J1.SHLD6 (SHIELD), J1.SHLD7 (SHIELD), J1.SHLD8 (SHIELD), J2.1, SW1.3 (S1), SW1.4 (S1)
PB0: IC2.11 ((AREF/!OC1A!/OC0A/AIN0/SDA/DI/MOSI)PB0), J3.4
PB1: IC2.12 ((OC1A/OC0B/AIN1/DO/MISO)PB1), J3.3
PB2: IC2.14 ((INT0/T0/ADC1/SCL/SCK)PB2), J3.2
PB3: IC2.2 ((XTAL1/CLKI/ADC3/!OC1B!)PB3), J2.3, R2.1
PB4: IC2.5 ((XTAL2/CLKO/ADC2/OC1B)PB4), J2.2, R3.1
PB5: IC2.1 ((!RESET!/DW/ADC0)PB5), J2.4, R1.1, SW1.1, SW1.2 (P1)
VBUS: J1.VBUS, VBUS.2

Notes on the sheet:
Released under the Creative Commons Attribution Share-Alike License. http://creativecommons.org/licenses/by-sa/4.0/ Designed by Stephan Watterott (Watterott electronic) Based on the original Nanite 85 design by Tim Böscke https://github.com/cpldcpu/Nanite
The used USB-Bootloader on the ATtiny85 is Micronucleus https://github.com/micronucleus/micronucleus
CZRER52C3V6 (3.6V <180pF) + 1k5 Pull-Up or uClamp2511T (3.1V 6pF) + 2k2 Pull-Up
Arduino
GND
VCC

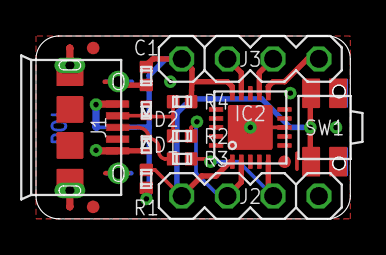
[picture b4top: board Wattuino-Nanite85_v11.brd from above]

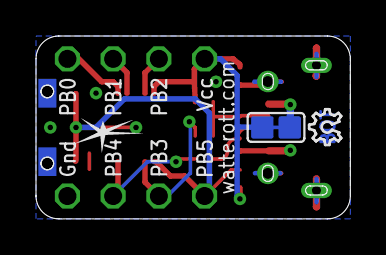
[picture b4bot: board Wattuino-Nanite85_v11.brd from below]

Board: 2 copper layers, 17.5 x 10.2 mm, 18 parts (3 on the bottom side), 11 nets.

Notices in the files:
software/Arduino/hardware/watterott/samd/variants/wattuino_rc/variant.cpp:
Copyright (c) 2014-2015 Arduino LLC.  All right reserved.
src/Arduino/hardware/atmega/avr/variants/leonardo/pins_arduino.h:
Copyright (c) 2007 David A. Mellis
